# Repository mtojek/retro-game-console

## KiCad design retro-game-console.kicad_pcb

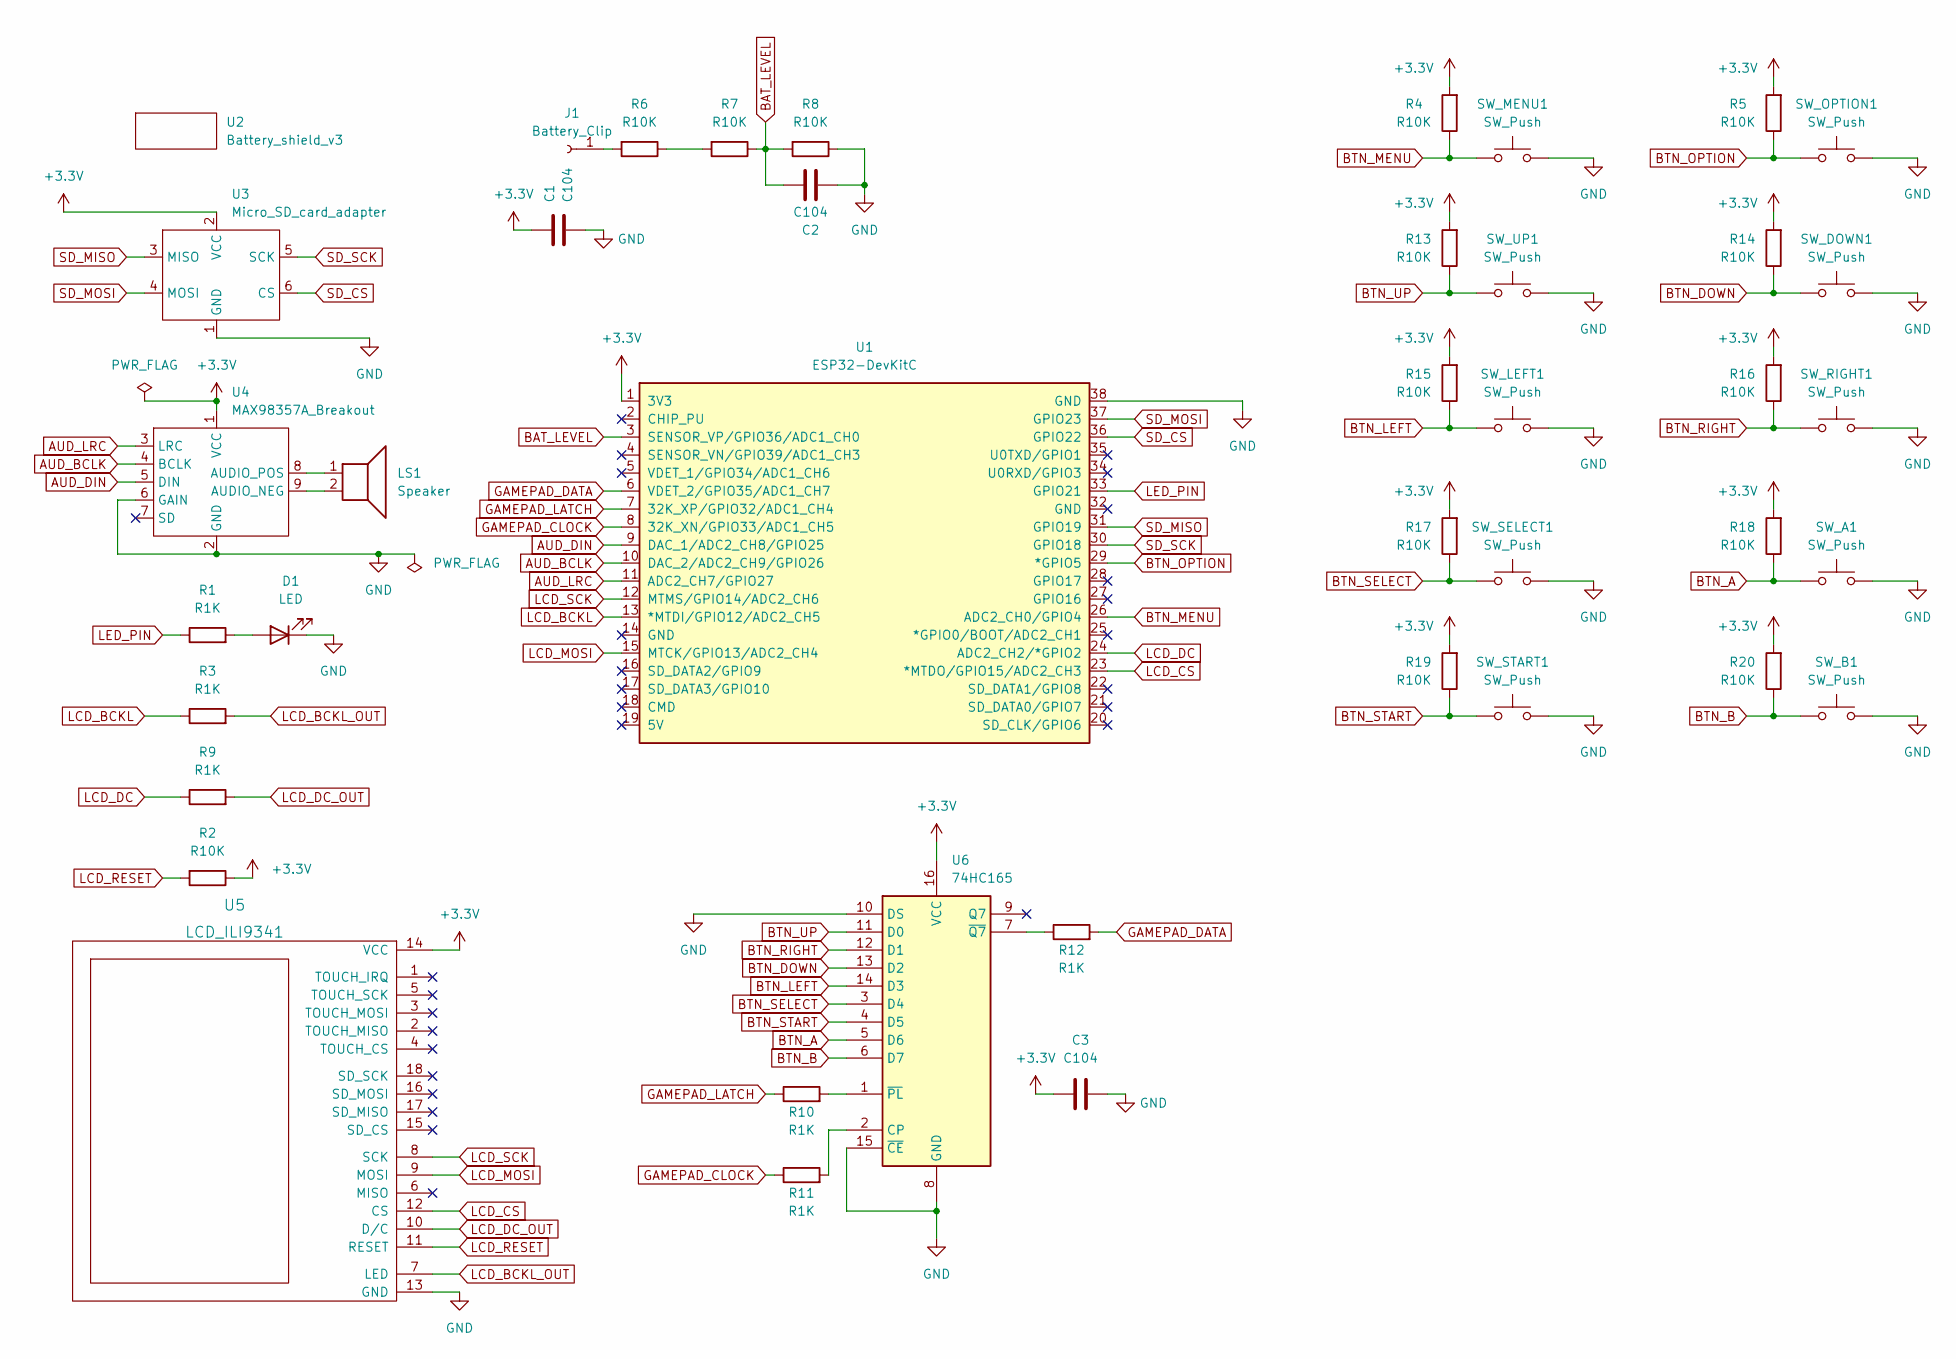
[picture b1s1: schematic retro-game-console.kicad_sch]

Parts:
C1, C2, C3: C104; C_Rect_L7.0mm_W3.5mm_P5.00mm
D1: LED; LED_D5.0mm
J1: Battery_Clip; PinSocket_1x01_P2.54mm_Vertical
LS1: Speaker
R1, R3, R9, R10, R11, R12: R1K; R_Axial_DIN0309_L9.0mm_D3.2mm_P12.70mm_Horizontal
R2, R4, R5, R6, R7, R8, R17, R19: R10K; R_Axial_DIN0309_L9.0mm_D3.2mm_P12.70mm_Horizontal
R13, R14, R15, R16, R18, R20: R10K; R_Axial_DIN0309_L9.0mm_D3.2mm_P15.24mm_Horizontal
SW_A1: SW_Push; SW_PUSH-12mm
SW_B1: SW_Push; SW_PUSH-12mm
SW_DOWN1: SW_Push; SW_PUSH-12mm
SW_LEFT1: SW_Push; SW_PUSH-12mm
SW_MENU1: SW_Push; SW_Push_1P1T_NO_6x6mm_H9.5mm
SW_OPTION1: SW_Push; SW_Push_1P1T_NO_6x6mm_H9.5mm
SW_RIGHT1: SW_Push; SW_PUSH-12mm
SW_SELECT1: SW_Push; SW_Push_1P1T_NO_6x6mm_H9.5mm
SW_START1: SW_Push; SW_Push_1P1T_NO_6x6mm_H9.5mm
SW_UP1: SW_Push; SW_PUSH-12mm
U1: ESP32-DevKitC
U2: Battery_shield_v3
U3: Micro_SD_card_adapter
U4: MAX98357A_Breakout
U5: LCD_ILI9341; LCD_2.4in
U6: 74HC165; DIP-16_W7.62mm_LongPads

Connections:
+3.3V: C1.2, C3.2, R2.1, R4.2, R5.2, R13.2, R14.2, R15.2, R16.2, R17.2, R18.2, R19.2, R20.2, U1.1 (3V3), U3.2 (VCC), U4.1 (VCC), U5.14 (VCC), U6.16 (VCC)
AUD_BCLK: U1.10 (DAC_2/ADC2_CH9/GPIO26), U4.4 (BCLK)
AUD_DIN: U1.9 (DAC_1/ADC2_CH8/GPIO25), U4.5 (DIN)
AUD_LRC: U1.11 (ADC2_CH7/GPIO27), U4.3 (LRC)
BAT_LEVEL: C2.2, R7.1, R8.2, U1.3 (SENSOR_VP/GPIO36/ADC1_CH0)
BTN_A: R18.1, SW_A1.1, U6.5 (D6)
BTN_B: R20.1, SW_B1.1, U6.6 (D7)
BTN_DOWN: R14.1, SW_DOWN1.1, U6.13 (D2)
BTN_LEFT: R15.1, SW_LEFT1.1, U6.14 (D3)
BTN_MENU: R4.1, SW_MENU1.1, U1.26 (ADC2_CH0/GPIO4)
BTN_OPTION: R5.1, SW_OPTION1.1, U1.29 (*GPIO5)
BTN_RIGHT: R16.1, SW_RIGHT1.1, U6.12 (D1)
BTN_SELECT: R17.1, SW_SELECT1.1, U6.3 (D4)
BTN_START: R19.1, SW_START1.1, U6.4 (D5)
BTN_UP: R13.1, SW_UP1.1, U6.11 (D0)
GAMEPAD_CLOCK: R11.1, U1.8 (32K_XN/GPIO33/ADC1_CH5)
GAMEPAD_DATA: R12.2, U1.6 (VDET_2/GPIO35/ADC1_CH7)
GAMEPAD_LATCH: R10.1, U1.7 (32K_XP/GPIO32/ADC1_CH4)
GND: C1.1, C2.1, C3.1, D1.1 (K), R8.1, SW_A1.2, SW_B1.2, SW_DOWN1.2, SW_LEFT1.2, SW_MENU1.2, SW_OPTION1.2, SW_RIGHT1.2, SW_SELECT1.2, SW_START1.2, SW_UP1.2, U1.38 (GND), U3.1 (GND), U4.2 (GND), U4.6 (GAIN), U5.13 (GND), U6.8 (GND), U6.10 (DS), U6.15 (~CE)
LCD_BCKL: R3.1, U1.13 (*MTDI/GPIO12/ADC2_CH5)
LCD_BCKL_OUT: R3.2, U5.7 (LED)
LCD_CS: U1.23 (*MTDO/GPIO15/ADC2_CH3), U5.12 (CS)
LCD_DC: R9.1, U1.24 (ADC2_CH2/*GPIO2)
LCD_DC_OUT: R9.2, U5.10 (D/C)
LCD_MOSI: U1.15 (MTCK/GPIO13/ADC2_CH4), U5.9 (MOSI)
LCD_RESET: R2.2, U5.11 (RESET)
LCD_SCK: U1.12 (MTMS/GPIO14/ADC2_CH6), U5.8 (SCK)
LED_PIN: R1.1, U1.33 (GPIO21)
unnamed: D1.2 (A), R1.2
unnamed: J1.1, R6.2
unnamed: LS1.1, U4.8 (AUDIO_POS)
unnamed: LS1.2, U4.9 (AUDIO_NEG)
unnamed: R6.1, R7.2
unnamed: R10.2, U6.1 (~PL)
unnamed: R11.2, U6.2 (CP)
unnamed: R12.1, U6.7 (~Q7)
SD_CS: U1.36 (GPIO22), U3.6 (CS)
SD_MISO: U1.31 (GPIO19), U3.3 (MISO)
SD_MOSI: U1.37 (GPIO23), U3.4 (MOSI)
SD_SCK: U1.30 (GPIO18), U3.5 (SCK)

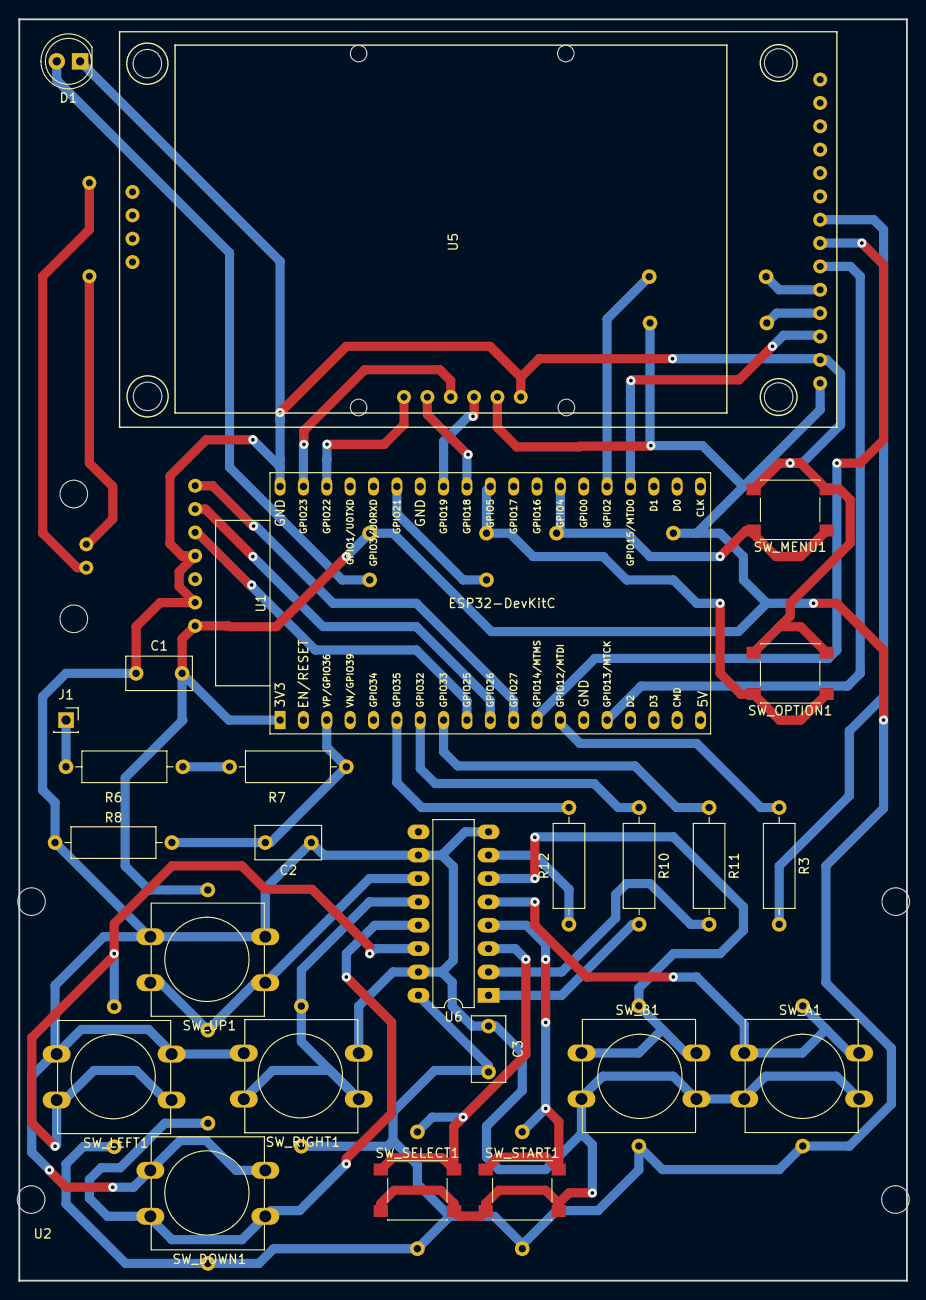
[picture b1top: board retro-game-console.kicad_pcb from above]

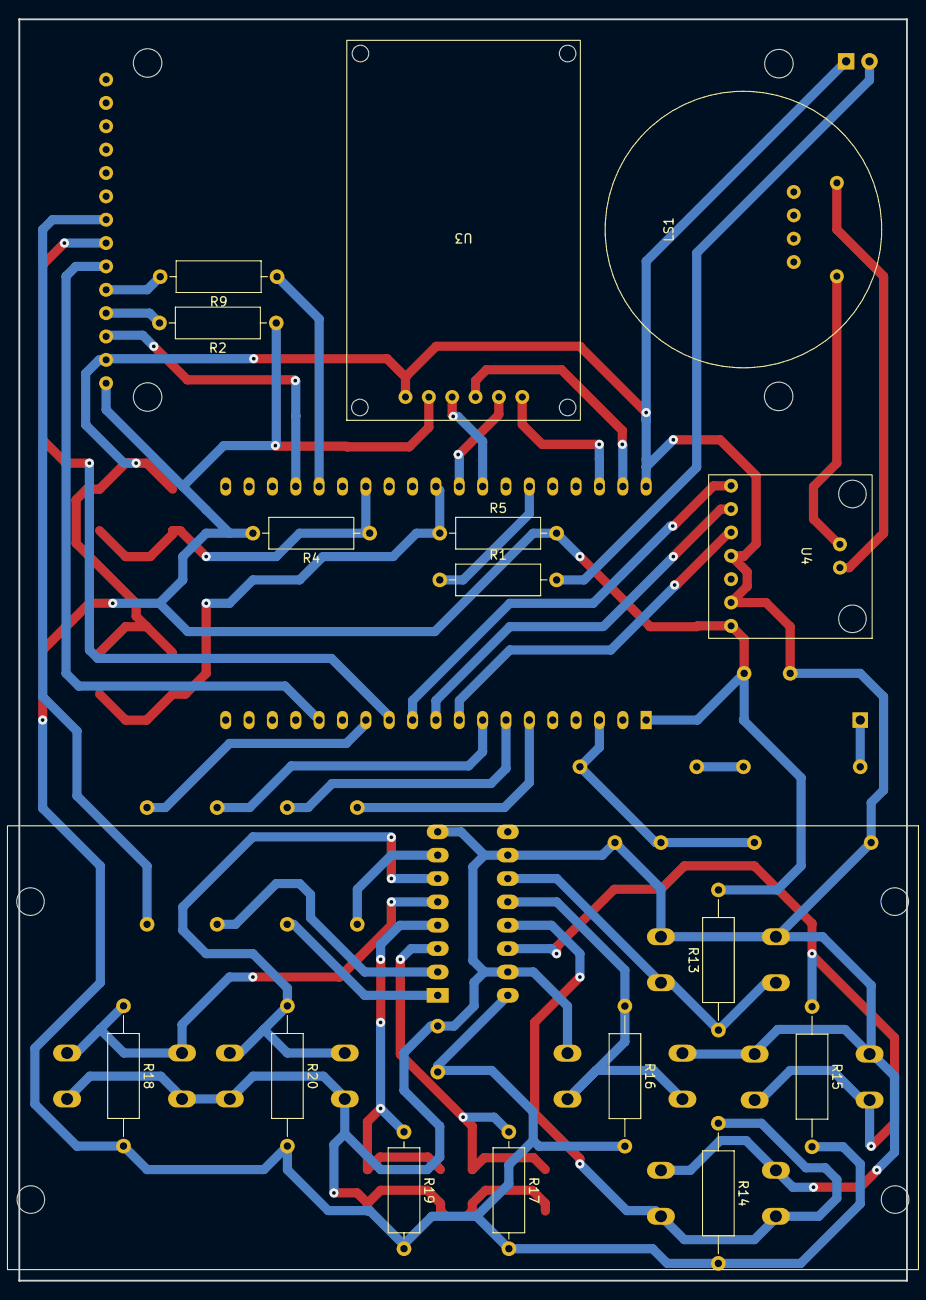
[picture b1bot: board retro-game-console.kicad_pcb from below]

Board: 2 copper layers, 96.5 x 137.2 mm, 42 parts (17 on the bottom side), 40 nets.

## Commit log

2022-12-16 More components
2022-12-17 All components are there
2022-12-27 Progress
2022-12-29 Schema done
2022-12-29 Schema
2023-01-01 Network in progress
2023-01-03 Before net
2023-01-08 Network finished
2023-01-08 Final v1
2023-01-08 Final v1.1
2023-01-14 snapshot
